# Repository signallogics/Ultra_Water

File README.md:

# Ultra_Water

A water level controller which indicates the current water level of the water tank and controls it according to the given set-points. This helps to save a lot of water where there is no automated water level control system hence saving valuable water and electricity.
 This contains Arduino code of the project, Schematic of the project and Eagle files of the project.

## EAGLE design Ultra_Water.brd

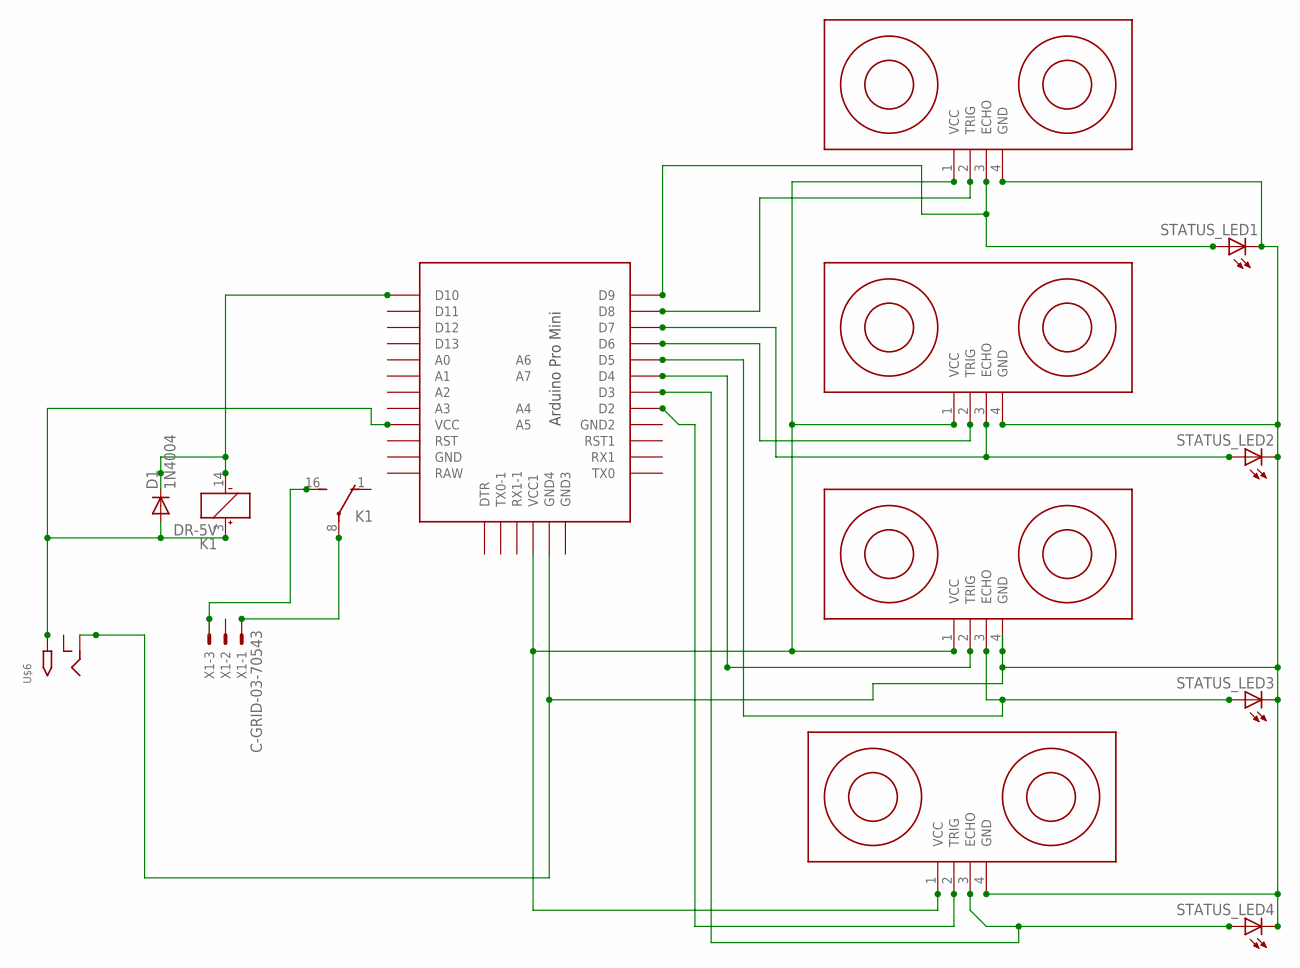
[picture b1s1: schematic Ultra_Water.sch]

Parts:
D1: 1N4004; DO41-10
K1: DR-5V; DR-1
STATUS_LED1, STATUS_LED2, STATUS_LED3, STATUS_LED4: LED5MM
U$1: PRO-MINI-2
U$2, U$3, U$4, U$5: ULTRASONIC-HC-SR04
U$6: 2.1MMJACKTHM; PJ-102A
X1: C-GRID-03-70543; 70543-03

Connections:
unnamed: U$1.VCC1, U$2.1 (VCC), U$3.1 (VCC), U$4.1 (VCC), U$5.1 (VCC)
unnamed: U$1.D4, U$4.2 (TRIG)
unnamed: STATUS_LED2.A, U$1.D7, U$3.3 (ECHO)
unnamed: STATUS_LED1.A, U$1.D9, U$2.3 (ECHO)
unnamed: STATUS_LED4.A, U$1.D3, U$5.3 (ECHO)
unnamed: D1.C, K1.14 (-), U$1.D10
unnamed: D1.A, K1.3 (+), U$1.VCC, U$6.TIP
unnamed: K1.8, X1.1
unnamed: STATUS_LED1.K (C), STATUS_LED2.K (C), STATUS_LED3.K (C), STATUS_LED4.K (C), U$1.GND3 (GND4), U$2.4 (GND), U$3.4 (GND), U$4.4 (GND), U$5.4 (GND), U$6.RING
unnamed: K1.16 (S), X1.3
unnamed: U$1.D8, U$2.2 (TRIG)
unnamed: U$1.D2, U$5.2 (TRIG)
unnamed: U$1.D6, U$3.2 (TRIG)
unnamed: STATUS_LED3.A, U$1.D5, U$4.3 (ECHO)

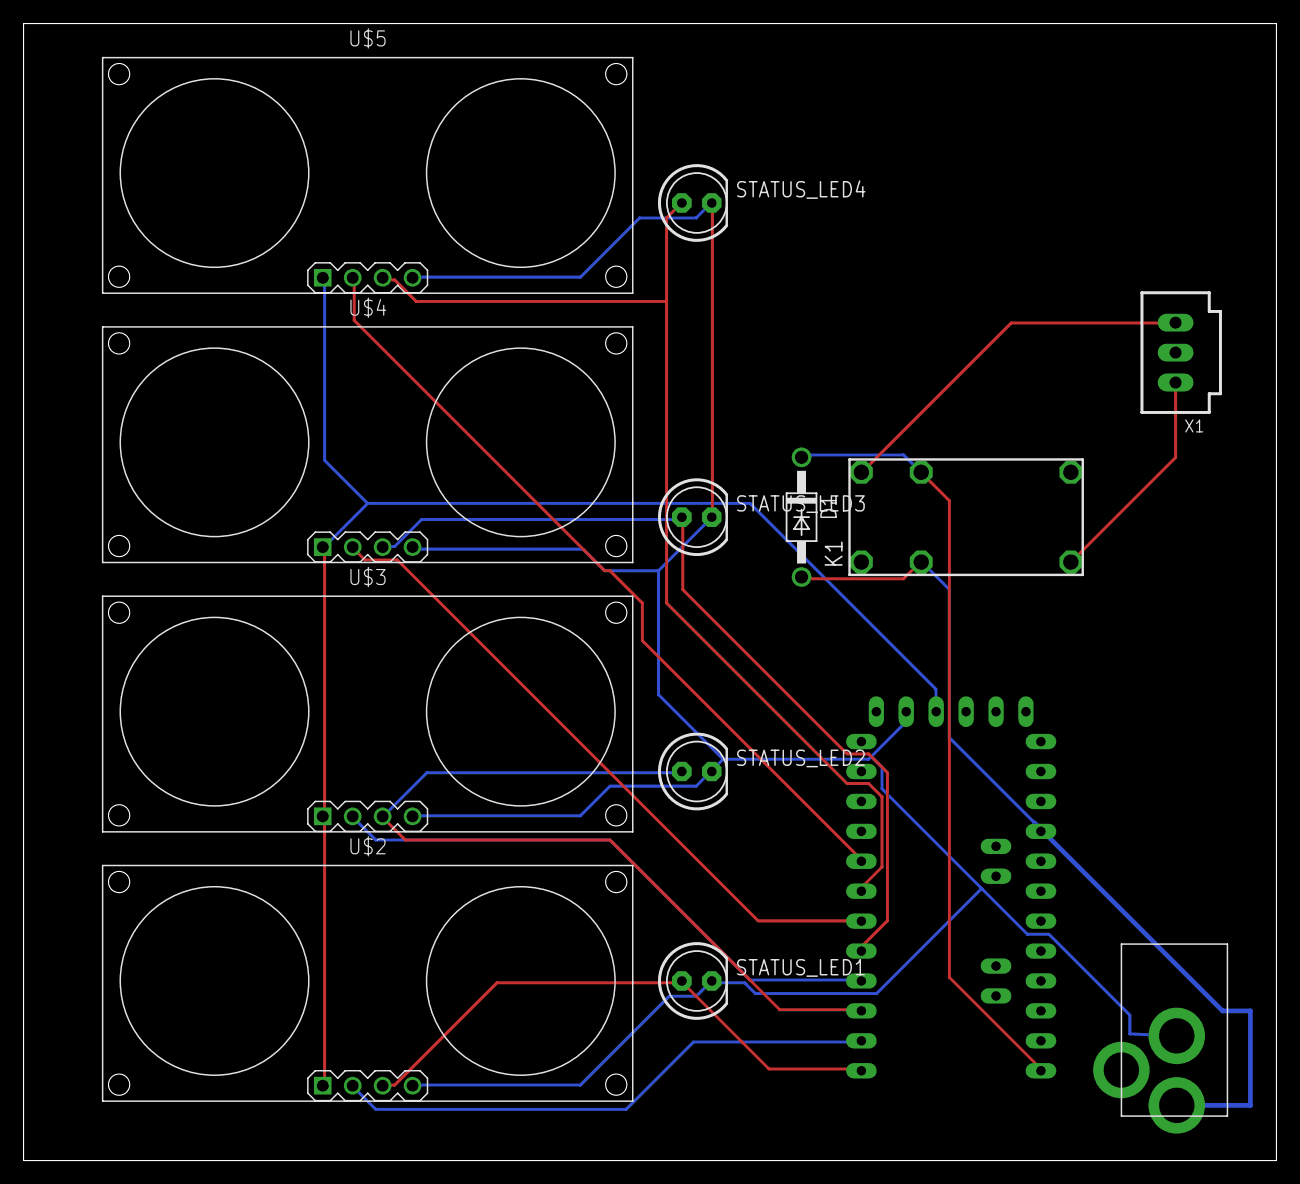
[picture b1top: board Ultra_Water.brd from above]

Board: 2 copper layers, 106.3 x 96.5 mm, 13 parts (0 on the bottom side), 14 nets.

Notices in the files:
parts and their libraries:
diy-modules: Released under the Creative Commons Attribution 4.0 International License: http://creativecommons.org/licenses/by/4.0
